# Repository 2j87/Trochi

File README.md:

# Trochi

Trochi is a coreless-motor drone mainboard designed as a shield for the ESP32-S3 Supermini, controlled over WiFi/ESP-NOW using the ESP-Drone firmware stack (no dedicated RC receiver).

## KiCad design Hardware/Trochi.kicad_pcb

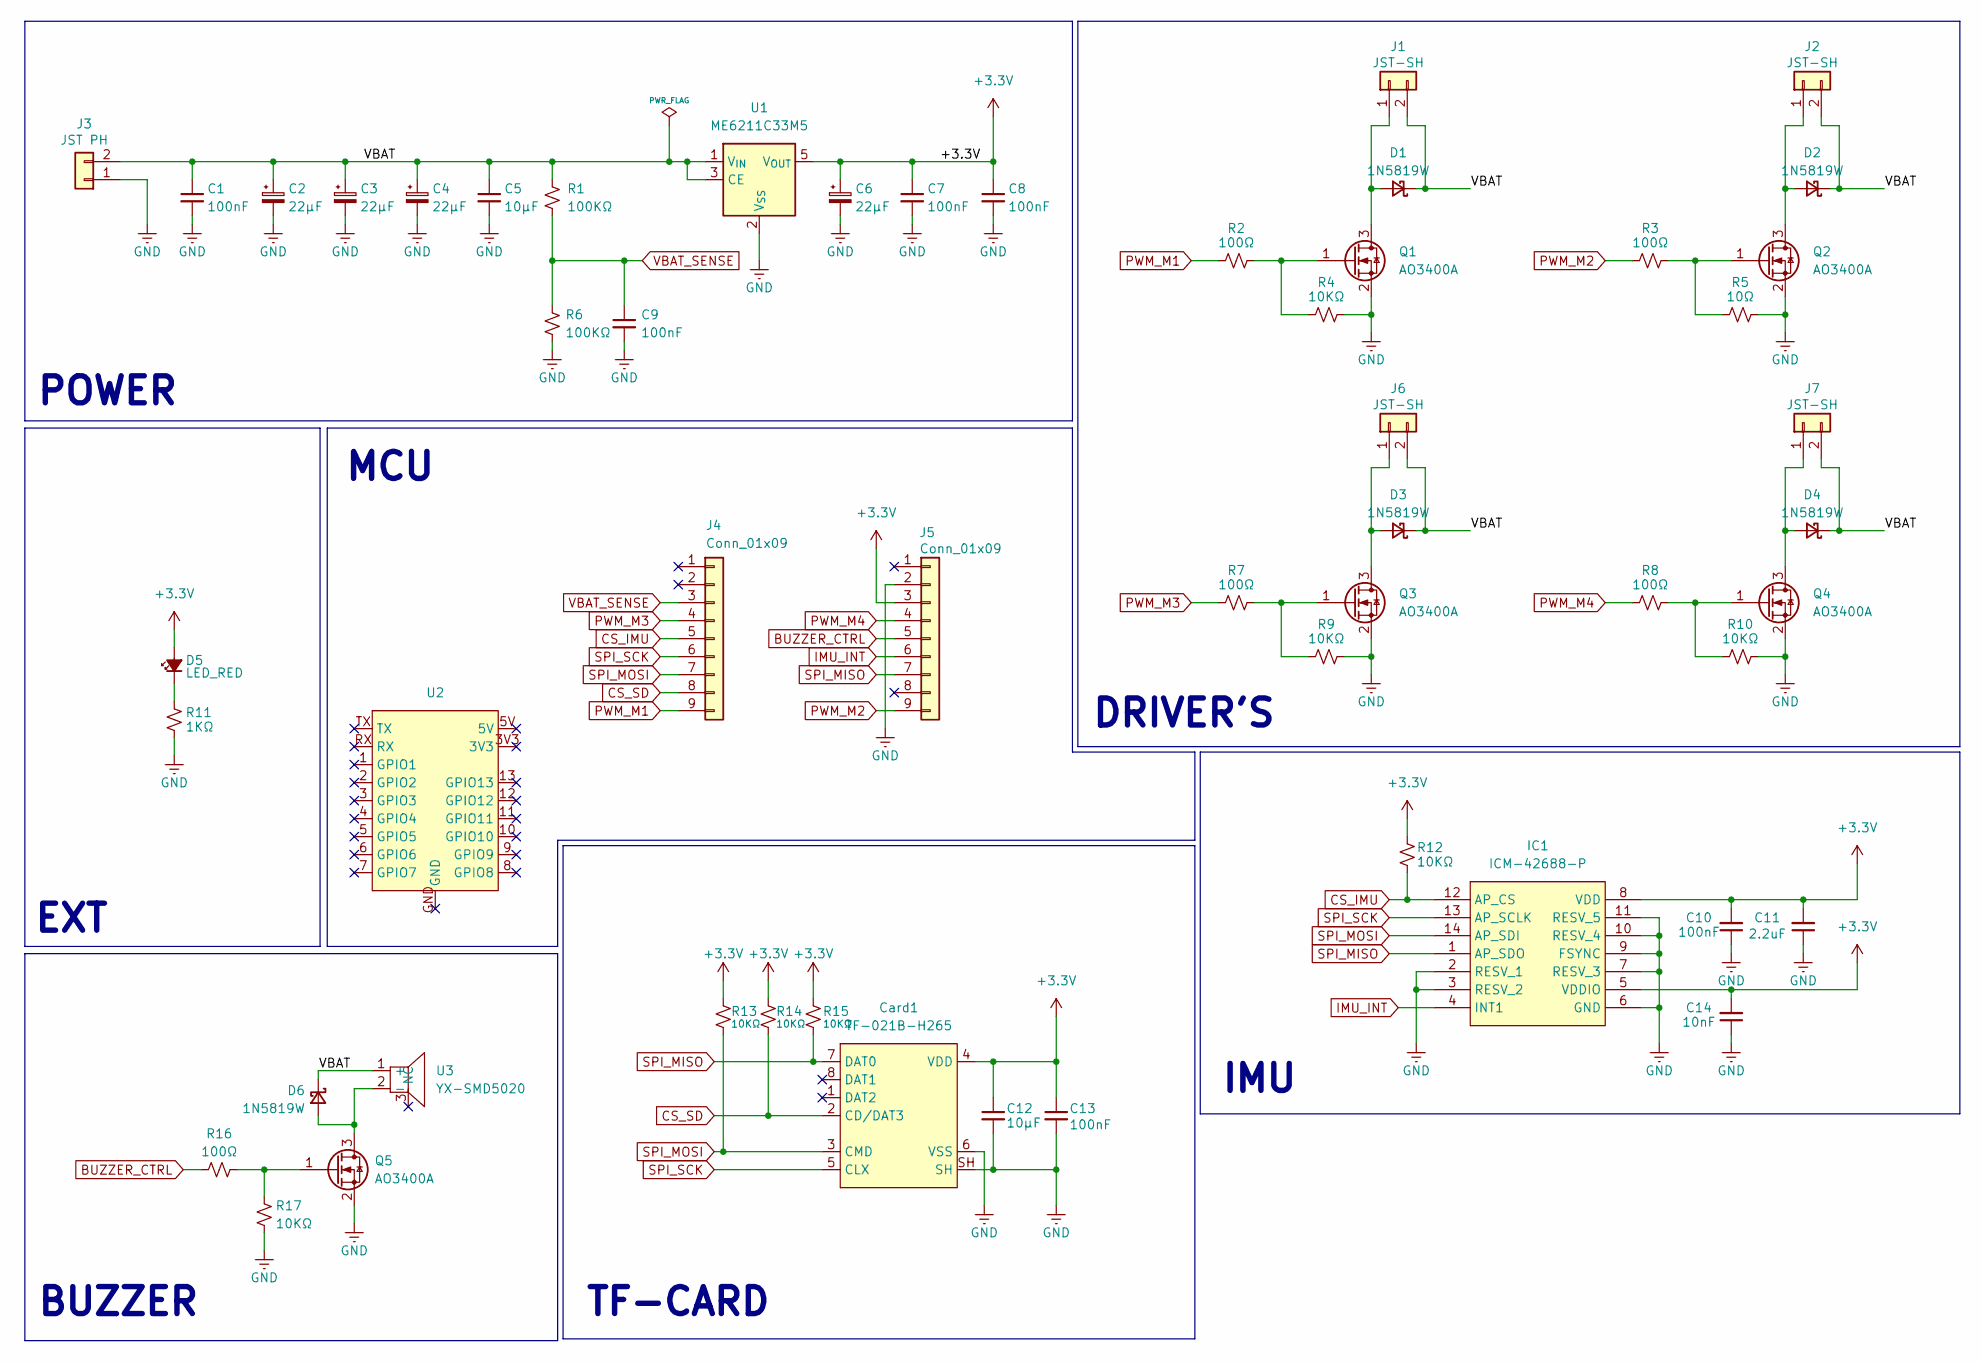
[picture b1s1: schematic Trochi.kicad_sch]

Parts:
C1, C7, C8, C9, C10, C13: 100nF; C_0402_1005Metric; Part Number C1525
C2, C3, C4: 22µF; C_0603_1608Metric; Part Number C15008
C5, C12: 10µF; C_0402_1005Metric; Part Number C15525
C6: 22µF; C_0805_2012Metric; Part Number C318688
C11: 2.2uF; C_0402_1005Metric; Part Number C1525
C14: 10nF; C_0402_1005Metric; Part Number C1525
Card1: TF-021B-H265; TF-SMD_TF-021B-H265; MPN TF-021B-H265; LCSC Part C498185
D1, D2, D3, D4, D6: 1N5819W; D_SOD-123; Part Number C2480
D5: LED_RED; LED_0603_1608Metric; Part Number C2286
IC1: ICM-42688-P; Manufacturer_Part_Number ICM-42688-P; Mouser Part Number 410-ICM-42688-P
J1, J2, J6, J7: JST-SH; CONN-SMD_2P-P1.00_SM02B-SRSS-TB-LF-SN
J3: JST PH; CONN-SMD_P2.00_S2B-PH-SM4-TB-LF-SN; Part Number C295747
J4, J5: Conn_01x09; PinHeader_1x09_P2.54mm_Vertical
Q1, Q2, Q4, Q5: AO3400A; SOT-23; Part Number C181090
Q3: AO3400A; SOT-23; LCSC C181090
R1: 100KΩ; R_0402_1005Metric; Part Number C60491
R2, R3, R7, R8: 100Ω; R_0402_1005Metric
R4, R9, R10, R12: 10KΩ; R_0402_1005Metric
R5: 10Ω; R_0402_1005Metric
R6: 100KΩ; R_0402_1005Metric
R11: 1KΩ; R_0402_1005Metric; Part Number C2889341
R13, R14, R15, R17: 10KΩ; R_0402_1005Metric; Part Number C25744
R16: 100Ω; R_0402_1005Metric; Part Number C25076
U1: ME6211C33M5; SOT-23-5; Part Number C82942
U2: esp32_s3_supermini
U3: YX-SMD5020; BUZ-SMD_3P_L5.0-W5.0-P3.50-TL; MPN YX-SMD5020

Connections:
+3.3V: C6.1, C7.1, C8.1, C10.2, C11.2, C12.1, C13.1, C14.2, Card1.4 (VDD), D5.2 (A), IC1.5 (VDDIO), IC1.8 (VDD), J5.3, R12.1, R13.1, R14.1, R15.1, U1.5 (V_{OUT})
/VBAT: C1.1, C2.1, C3.1, C4.1, C5.1, D1.1 (K), D2.1 (K), D3.1 (K), D4.1 (K), D6.1 (K), J1.2, J2.2, J3.2, J6.2, J7.2, R1.1, U1.1 (V_{IN}), U1.3 (CE), U3.1 (+)
BUZZER_CTRL: J5.5, R16.1
CS_IMU: IC1.12 (AP_CS), J4.5, R12.2
CS_SD: Card1.2 (CD/DAT3), J4.8, R14.2
GND: C1.2, C2.2, C3.2, C4.2, C5.2, C6.2, C7.2, C8.2, C9.2, C10.1, C11.1, C12.2, C13.2, C14.1, Card1.6 (VSS), Card1.SH, IC1.2 (RESV_1), IC1.3 (RESV_2), IC1.6 (GND), IC1.7 (RESV_3), IC1.9 (FSYNC), IC1.10 (RESV_4), IC1.11 (RESV_5), J3.1, J5.2, Q1.2 (S), Q2.2 (S), Q3.2 (S), Q4.2 (S), Q5.2 (S), R4.2, R5.2, R6.2, R9.2, R10.2, R11.2, R17.2, U1.2 (V_{SS})
IMU_INT: IC1.4 (INT1), J5.6
unnamed: D1.2 (A), J1.1, Q1.3 (D)
unnamed: D2.2 (A), J2.1, Q2.3 (D)
unnamed: D3.2 (A), J6.1, Q3.3 (D)
unnamed: D4.2 (A), J7.1, Q4.3 (D)
unnamed: D5.1 (K), R11.1
unnamed: D6.2 (A), Q5.3 (D), U3.2 (-)
unnamed: Q1.1 (G), R2.2, R4.1
unnamed: Q2.1 (G), R3.2, R5.1
unnamed: Q3.1 (G), R7.2, R9.1
unnamed: Q4.1 (G), R8.2, R10.1
unnamed: Q5.1 (G), R16.2, R17.1
PWM_M1: J4.9, R2.1
PWM_M2: J5.9, R3.1
PWM_M3: J4.4, R7.1
PWM_M4: J5.4, R8.1
SPI_MISO: Card1.7 (DAT0), IC1.1 (AP_SDO), J5.7, R15.2
SPI_MOSI: Card1.3 (CMD), IC1.14 (AP_SDI), J4.7, R13.2
SPI_SCK: Card1.5 (CLX), IC1.13 (AP_SCLK), J4.6
VBAT_SENSE: C9.1, J4.3, R1.2, R6.1

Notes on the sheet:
MCU
IMU
POWER
EXT
TF-CARD
DRIVER'S
BUZZER

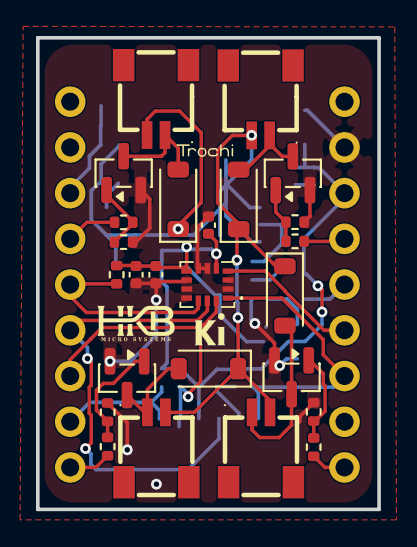
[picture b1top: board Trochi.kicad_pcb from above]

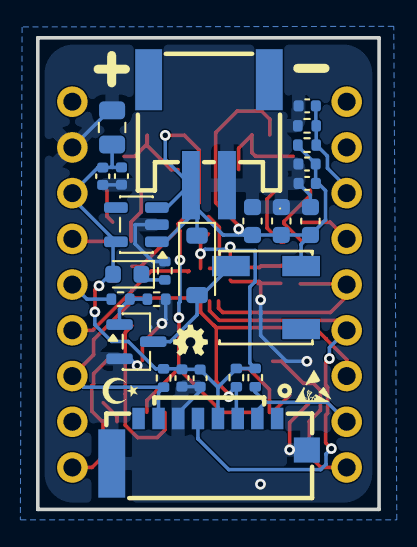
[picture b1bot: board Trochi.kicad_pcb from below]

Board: 2 copper layers, 19.0 x 26.2 mm, 53 parts (26 on the bottom side), 26 nets.
